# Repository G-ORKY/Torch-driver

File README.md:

The LED torch with NV4WB35AM.
Use LM3401 as the current-fixed DC-DC controller.
Use STC15L104W as the pwm controller and for battery protection.

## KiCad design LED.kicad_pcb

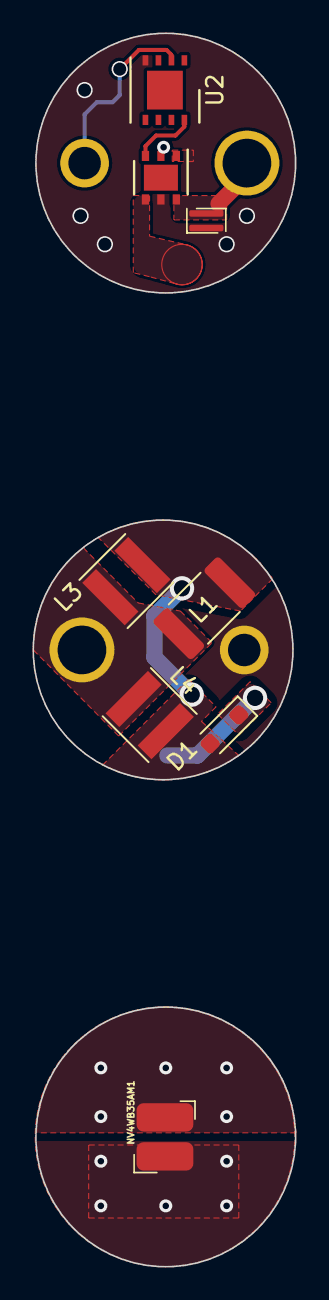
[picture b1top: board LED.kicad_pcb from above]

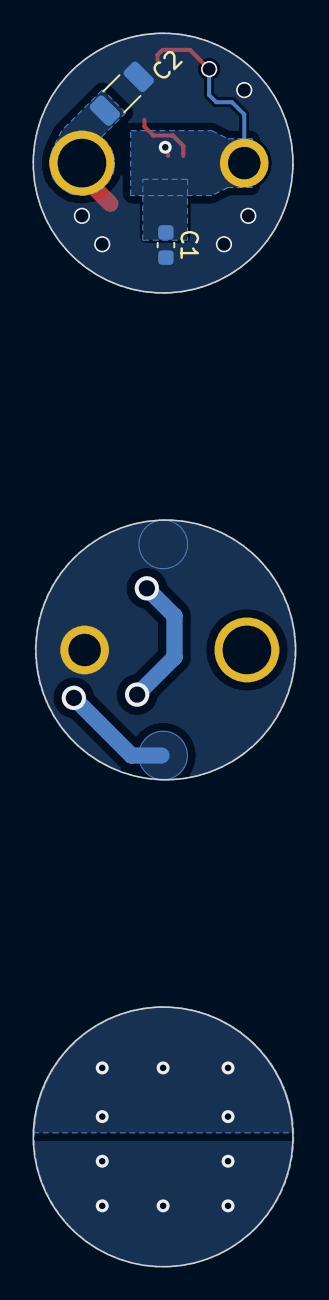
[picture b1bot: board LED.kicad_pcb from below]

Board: 2 copper layers, 16.2 x 76.0 mm, 10 parts (2 on the bottom side), 6 nets.

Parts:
C1: 10uF; C_0603_1608Metric
C2: 47uF; C_1206_3216Metric
D1: D; D_SOD-323_HandSoldering
L1: 27uH; L_1812_4532Metric_Pad1.30x3.40mm_HandSolder
L3, L4: 22uH; L_Taiyo-Yuden_MD-4040
LM3401: WSON-6-1EP_3x3mm_P0.95mm
NV4WB35AM1: NV4WB35AM
R1: 137m; SMD-0508
U2: DFN-8-1EP_4x4mm_P0.8mm_EP2.39x2.21mm

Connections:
+BATT: C1.1, L1.1, L3.1, L4.1, LM3401.2 (Vin), U2.2 (VCC)
-BATT: C1.2, C2.2, LM3401.5 (AGND), R1.2, U2.4 (GND)
unnamed: D1.2 (A), L1.2, L3.2, L4.2, LM3401.4 (SW)
unnamed: D1.1 (K), NV4WB35AM1.1 (Vin)
unnamed: LM3401.3 (DIM), U2.8 (RSTOUT_LOW/INT1/P3.3)
unnamed: C2.1, LM3401.6 (FB), NV4WB35AM1.2 (GND), R1.1

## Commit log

2024-07-23 create the project
